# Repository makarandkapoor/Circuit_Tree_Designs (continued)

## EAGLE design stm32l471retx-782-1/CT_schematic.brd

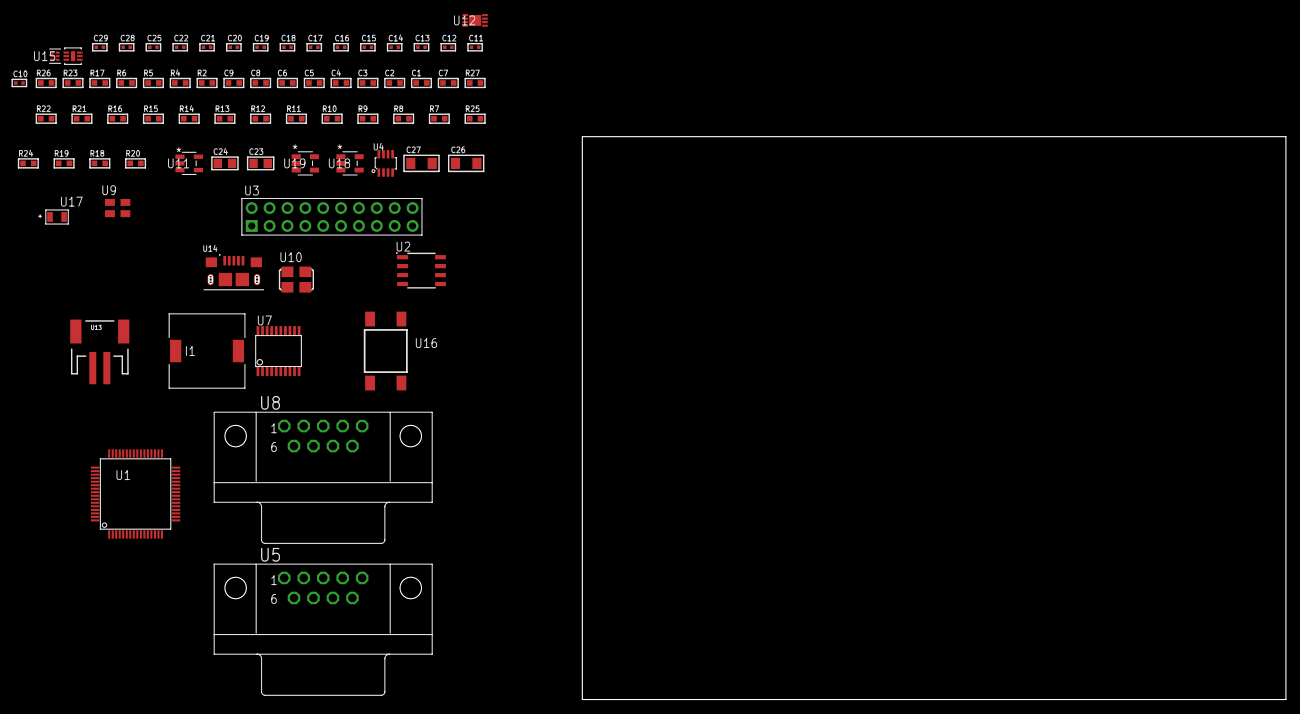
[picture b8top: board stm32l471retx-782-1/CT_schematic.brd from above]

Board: 2 copper layers, 74 parts (0 on the bottom side), 53 nets, no tracks yet.

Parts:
C1, C9: 1e-06; C0603
C2, C3, C4, C5, C6: 1e-07; C0603
C7: 4.7e-06; C0603
C8: 1e-08; C0603
C10, C21, C22, C28, C29: 1e-08; C0402
C11, C12, C13, C14, C15, C16, C17, C18, C19, C20, C25: 1e-07; C0402
C23, C24: 1e-05; C0805
C26, C27: 1e-05; C1206
I1: 3.8e-06; DR1040
R2: 1000.0; R0603
R4: 4700.0; R0603
R5, R6: 2200.0; R0603
R7, R8, R9, R10, R11, R12, R13, R14, R15, R16, R21, R22, R27: 10000.0; R0603
R17: 120.0; R0603
R18: 100000.0; R0603
R19: 220000.0; R0603
R20: 1000000.0; R0603
R23: 9100.0; R0603
R24: 680000.0; R0603
R25: 120000.0; R0603
R26: 2000.0; R0603
U1: STM32L471RET6; LQFP64
U2: AT25512N-SH-T; SOIC-8
U3: TST-110-05-T-D-RA
U4: MAX3051EKA+T; SOT-23-8
U5, U8: 182-009-113R531; 182-009-MALE
U6: SI7006-A20-IM; DFN-6
U7: SP3203ECY-L/TR; TSSOP20-I
U9: ASEK-32.768KHz-ECST; ASEK
U10: ASFL1-25MHZ-NCS; ASFL1
U11: ltc3406es5; TSOT-23-5
U12: MCP73831T-2ACI/MC; DFN8_2X3MC
U13: S2B-PH-SM4-TB(LF)(SN); JST-2-SMD
U14: 10118193-0001LF; FCI_10118193-0001LF
U15: TPS3895ADRYR; SON-6
U16: 4-1437565-2; SW_4-1437565-2
U17: Q65110A2395; LGM67K-G1J2-24-Z
U18, U19: nc7sz125m5x; NC7SZ125M5X

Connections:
CLK_U1_3: U1.3, U9.3
CLK_U1_5: U1.5, U10.3
GND: C1.2, C2.2, C3.2, C4.2, C5.2, C6.2, C7.2, C8.2, C9.2, C10.2, C11.2, C12.2, C13.2, C14.2, C15.2, C16.2, C19.2, C20.2, C21.2, C22.2, C23.2, C24.1, C24.2, C25.2, C26.2, C27.2, C28.2, C29.2, R2.2, R7.2, R16.2, R18.2, R19.2, R23.2, R25.2, R26.2, U1.12, U1.18, U1.31, U1.47, U1.63, U2.4, U3.4, U3.6, U3.8, U3.10, U3.12, U3.14, U3.16, U3.18, U3.20, U4.2, U5.5, U6.2, U6.7, U7.18, U8.5, U9.2, U10.2, U11.2, U12.6, U12.9, U13.2, U14.5, U14.6, U14.7, U14.8, U14.9, U15.2, U17.C, U18.2, U18.3, U19.1, U19.3
INPUT_USBPOWER_5V: C26.1, R27.2, U12.1, U12.2, U14.1
NET_U1_7: R4.1, U1.7, U19.4
NET_U1_58: R5.1, U1.58, U6.6
NET_U1_59: R6.1, U1.59, U6.1
NET_U1_60: R7.1, U1.60
NET_U1_62: U16.3, U16.4
NET_U2_3: R8.1, U2.3
NET_U2_7: R10.1, U2.7
NET_U3_9: R14.1, U3.9
NET_U3_19: R16.1, U3.19
NET_U4_6: R17.2, U4.6
NET_U4_8: R18.1, U4.8
NET_U5_2: R17.2, U4.6, U5.2
NET_U5_3: R17.1, U4.7, U5.3
NET_U7_1: C17.1, U7.1
NET_U7_2: C19.1, U7.2
NET_U7_3: C17.2, U7.3
NET_U7_4: C18.1, U7.4
NET_U7_5: C18.2, U7.5
NET_U7_6: C20.1, U7.6
NET_U8_2: U7.14, U8.2
NET_U8_3: U7.17, U8.3
NET_U8_7: U7.13, U8.7
NET_U8_8: U7.16, U8.8
NET_U11_3: I1.1, U11.3
NET_U11_5: R19.1, R20.1, U11.5
NET_U11_ATNET_3: I1.2, R20.2
NET_U12_5: R27.1, U12.5
NET_U12_8: R26.1, U12.8
NET_U15_1: R22.1, R23.1, U15.1
NET_U15_3: R24.2, R25.1, U15.3
NET_U15_4: R21.1, U15.4, U18.4, U19.2
NET_U16_1: R2.1, U16.1, U16.2
PROC_CAN1_RX: U1.44, U4.4
PROC_CAN1_TX: U1.45, U4.1
PROC_LPUART1_CTS: U1.34, U7.8
PROC_LPUART1_RTS: U1.33, U7.10
PROC_LPUART1_RX: U1.8, U7.11
PROC_LPUART1_TX: U1.9, U7.7
PROC_SPI1_MISO: U1.22, U2.2
PROC_SPI1_MOSI: U1.23, U2.5
PROC_SPI1_NSS: R9.1, U1.20, U2.1
PROC_SPI1_SCK: U1.21, U2.6
PROC_SYS_JTDI: R12.1, U1.50, U3.5
PROC_SYS_JTDO_SWO: U1.55, U3.13
PROC_SYS_JTMS_SWDIO: R13.1, U1.46, U3.7
PROC_SYS_JTRST: R11.1, U1.56, U3.3
RST_OUT_U3_SRESET_B: R15.1, U3.15, U18.1
VCC_S1_3V7: C23.1, C27.1, U11.4, U12.3, U12.4, U13.1
VCC_TIER1_3V3: C1.1, C2.1, C3.1, C4.1, C5.1, C6.1, C7.1, C8.1, C9.1, C10.1, C11.1, C12.1, C13.1, C14.1, C15.1, C16.1, C21.1, C22.1, C24.2, C25.1, C28.1, C29.1, I1.2, R4.2, R5.2, R6.2, R8.2, R9.2, R10.2, R11.2, R12.2, R13.2, R14.2, R15.2, R20.2, R21.2, R22.2, R24.1, U1.1, U1.13, U1.19, U1.32, U1.48, U1.64, U2.8, U3.1, U3.2, U4.3, U6.5, U7.12, U7.19, U9.4, U10.4, U15.6, U18.5, U19.5
